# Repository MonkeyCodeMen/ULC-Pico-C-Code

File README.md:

# **ULC Pico   (Universal Light Controller on Raspberry Pico)**

All started with the purchasing of Raspberry Pico RP2040 in 2023. 

a fascinating dual core processor for less than 5€ (gosh do you know what we have paied for Z80 or 68K when I started with µController) .. congratulation to the raspberry foundation good job

The Arduino IDE beacomes to small for this number files so I changed to Visual Studio Code with PlatformIO
.. fascinating all for free .. and the integration of RP2040 from maxgerhardt outstanding .. Thanks a lot

I tried several other things like:

+ Rapberry Pico Debuger 
+ Unity test
+ embedded dual core arcitecture With debugging 
+ LED stripes, RGB LED Stripes, WS2812B LED stripes, WS2812B LED Matrix
+ SD card
+ Advent calender
+ Real Time Clock
+ SPI Display
+ I2C Slave (Arduino Nano)
+ I2C keyboard
+ GIF animations of WS2812B Matrix
+ advent calendar with gifs

.. I think I show you a picture of the current state:

I just want to explore how it works and it lead to this  .. but it will not be the end, it just reached a state where I decided to make it public to give something back to the community, in the hope it may be usefull for somebody. 
And don’t forget: always stay curious and persistent. The best way to learn is through mistakes. But only those who try something new and unfamiliar can make mistakes to learn from. Every day without learning something is a lost day.

So, search behind every tree and under very stone for the three-headed monkey, and if you need a boat, just ask for Stan.

The project keeps growing and growing .. I needed a PCB .. I found KiCad :
@KiCad Team .. a professional layout tool for free .. great work ... 

there were now a lot of components so I needed a hosuing 
.. you will not belief there is a free M-CAD tool : freecad 

I build all in wood an milled it on my MP CNC (a nice free project for CNC machine please look for it)
And this is the final result:

and what can I do ?
----------------
mainly it control several types of LED (a lot of them)

one example a advent calendar for nurds:

some more details:

---

## **Table of Contents**
- [System architecture](#system-architecture)
- [Software architecture](#software-architecture)
- [Required Libraries](#required-libraries)
- [Installation](#installation)
- [Usage](#usage)
- [Configuration](#configuration)
- [Unit Test](#unit-test)
- [Contributing](#contributing)
- [License](#license)

---
## **System architecture**

---
## **Software architecture**

I staied with the Arduino loop concept and designed the most classes in this manner. This is not suitable for hard real time rqeuirement, but it is easy and with the performance of the two cores of the RP2040 it is amazing what is possible.

But from my experience I use during one loop run a fixed time (now). I freeze this time at the begin of the loop and pass it than to every module that is been called in this loop. 

In addition to that I have a favor for the rough concept of state-machine with init run etc... 

For more details please refer the comment of the individual classes.

ToDo description to : 
+ multi core problems - MUTEX handling 

---

## **Required Libraries**

Below is a list of the libraries or frameworks required for the project to run. Make sure to install them before proceeding.

Many thanks to all the amazing developers of these libraries. Based on this foundation, it is possible to create larger projects like this one with a moderate amount of time. This enables significantly more functionality than would have been achievable by a single person alone.

All Lib's will be installed by PlatformIO based on ini file .. perfect .. @PlatforIO team: outstanding job, i know several professional tools from automobile industry that can not do this !!!!

### from Arduino:
+ Arduino base
+ wire
+ spi
+ SD

### RP2040 Toolchain 
https://github.com/maxgerhardt/platform-raspberrypi.git

### form adafruit: Adafruit BusIO @ ^1.16.2
+ RTClib @ ^2.1.4
+ Adafruit NeoMatrix @ ^1.3.3
  
### form bodmer:
+ TFT_eSPI @ ^2.5.43

### from kitesurfer1404:
+ WS2812FX @ ^1.4.4
  A beautiful and extensive library with many animations for intelligent RGB LEDs. Truly professional and exceptionally impressive work. Thank you so much for making something like this available!
  
### bitbank2:
+ AnimatedGIF @ ^2.1.1
  a real handy lib to handle GIF's thanks .. It would have cost me several monthes to do somthing that will be for sure not at this level ... Thanks
  
### robtillaart:
+ CRC @ ^1.0.3

### bblanchon:
+ ArduinoJson @ ^7.2.1

@all LIB authors .. great job, please keep up this good work 

---

## **Installation**

### **Prerequisites**
- SW: 
+ install Visual Studio Code
+ in Visual Studio install PlatformIO extension
- HW:
+ Install Kicad 
- Mechanic:
+ Install freeCad

### **Steps**
1. clone this project from GitHub (you can use Visual Studio Code interface or download it per WEB interface)
   ```bash
   git clone https://github.com/MonkeyCodeMen/ULC-Pico-C-Code.git

---

## **Configuration**

ToDo

---

## **Unit Test**

ToDo

---

## **License**

The MIT License (MIT)

Copyright (c) 2024 MonkeyCodeMen@GitHub

Permission is hereby granted, free of charge, to any person obtaining a copy
of this software and associated documentation files (the "Software"), to deal
in the Software without restriction, including without limitation the rights
to use, copy, modify, merge, publish, distribute, sublicense, and/or sell
copies of the Software, and to permit persons to whom the Software is
furnished to do so, subject to the following conditions:

The above copyright notice and this permission notice shall be included in all
copies or substantial portions of the Software.

THE SOFTWARE IS PROVIDED "AS IS", WITHOUT WARRANTY OF ANY KIND, EXPRESS OR
IMPLIED, INCLUDING BUT NOT LIMITED TO THE WARRANTIES OF MERCHANTABILITY,
FITNESS FOR A PARTICULAR PURPOSE AND NONINFRINGEMENT. IN NO EVENT SHALL THE
AUTHORS OR COPYRIGHT HOLDERS BE LIABLE FOR ANY CLAIM, DAMAGES OR OTHER
LIABILITY, WHETHER IN AN ACTION OF CONTRACT, TORT OR OTHERWISE, ARISING FROM,
OUT OF OR IN CONNECTION WITH THE SOFTWARE OR THE USE OR OTHER DEALINGS IN THE
SOFTWARE.

have fun !!

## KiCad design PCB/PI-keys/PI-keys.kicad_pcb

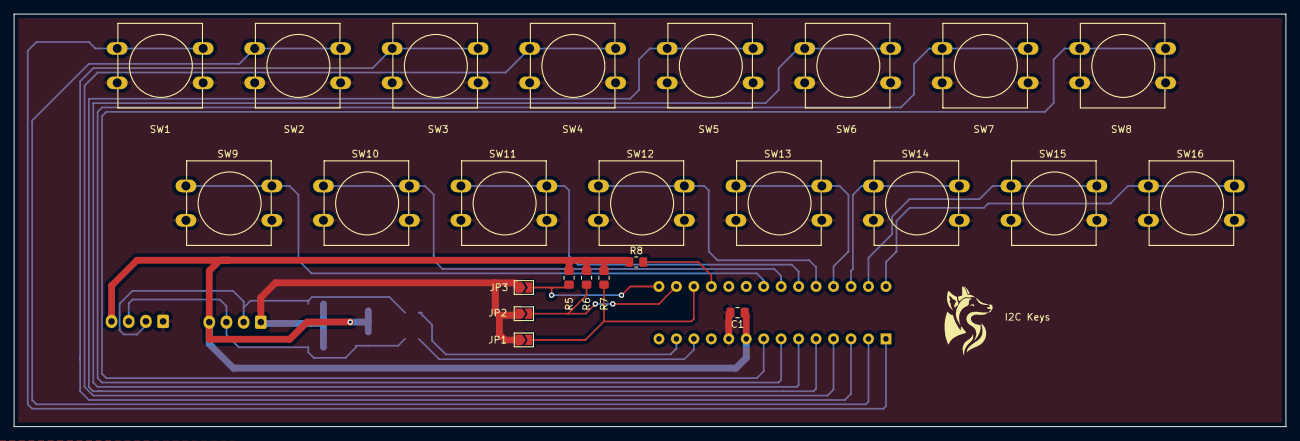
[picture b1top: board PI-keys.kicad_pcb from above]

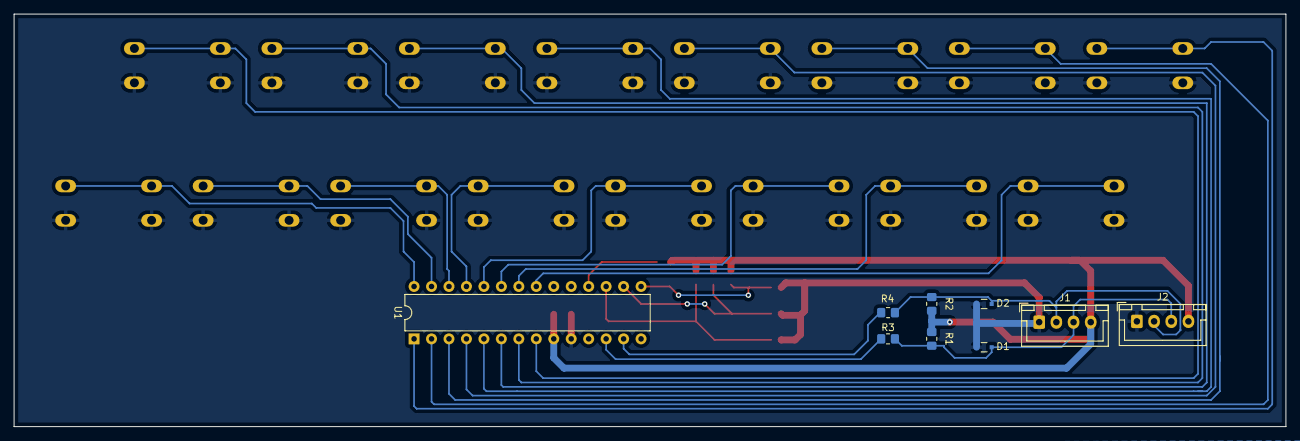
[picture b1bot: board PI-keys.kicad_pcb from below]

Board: 2 copper layers, 185.0 x 60.0 mm, 33 parts (9 on the bottom side), 26 nets.

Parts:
C1: 100nF; C_0805_2012Metric_Pad1.18x1.45mm_HandSolder
D1, D2: PESD5V0L1BA,115; Nexperia-SOD323-09_04_2018-0-0
J1, J2: Conn_01x04_Male; JST_XH_B4B-XH-A_1x04_P2.50mm_Vertical
JP1: A2; SolderJumper-2_P1.3mm_Open_TrianglePad1.0x1.5mm
JP2: A1; SolderJumper-2_P1.3mm_Open_TrianglePad1.0x1.5mm
JP3: A0; SolderJumper-2_P1.3mm_Open_TrianglePad1.0x1.5mm
R1, R2: 4K7; R_0805_2012Metric_Pad1.20x1.40mm_HandSolder
R3, R4: 0R; R_0805_2012Metric_Pad1.20x1.40mm_HandSolder
R5, R6, R7: 10K; R_0805_2012Metric_Pad1.20x1.40mm_HandSolder
R8: 100R; R_0805_2012Metric_Pad1.20x1.40mm_HandSolder
SW1, SW2, SW3, SW4, SW5, SW6, SW7, SW8, SW9, SW10, SW11, SW12, SW13, SW14, SW15, SW16: SW_Push_Dual; SW_PUSH-12mm
U1: MCP23017_SP; DIP-28_W7.62mm

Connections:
+3V3: C1.1, J1.4, J2.4, R1.1, R2.1, R5.1, R6.1, R7.1, R8.1, U1.9 (VDD)
GND: C1.2, D1.1, D2.1, J1.1, J2.1, JP1.1 (A), JP2.1 (A), JP3.1 (A), SW1.2, SW2.2, SW3.2, SW4.2, SW5.2, SW6.2, SW7.2, SW8.2, SW9.2, SW10.2, SW11.2, SW12.2, SW13.2, SW14.2, SW15.2, SW16.2, U1.10 (VSS)
unnamed: D1.2, J1.3, J2.3, R1.2, R3.2
unnamed: D2.2, J1.2, J2.2, R2.2, R4.2
unnamed: JP1.2 (B), R7.2, U1.17 (A2)
unnamed: JP2.2 (B), R6.2, U1.16 (A1)
unnamed: JP3.2 (B), R5.2, U1.15 (A0)
unnamed: R3.1, U1.12 (SCK)
unnamed: R4.1, U1.13 (SDA)
unnamed: SW1.1, U1.1 (GPB0)
unnamed: SW2.1, U1.2 (GPB1)
unnamed: SW3.1, U1.3 (GPB2)
unnamed: SW4.1, U1.4 (GPB3)
unnamed: SW5.1, U1.5 (GPB4)
unnamed: SW6.1, U1.6 (GPB5)
unnamed: SW7.1, U1.7 (GPB6)
unnamed: SW8.1, U1.8 (GPB7)
unnamed: SW9.1, U1.21 (GPA0)
unnamed: SW10.1, U1.22 (GPA1)
unnamed: SW11.1, U1.23 (GPA2)
unnamed: SW12.1, U1.24 (GPA3)
unnamed: SW13.1, U1.25 (GPA4)
unnamed: SW14.1, U1.26 (GPA5)
unnamed: SW15.1, U1.27 (GPA6)
unnamed: SW16.1, U1.28 (GPA7)
unnamed: R8.2, U1.18 (~RESET)

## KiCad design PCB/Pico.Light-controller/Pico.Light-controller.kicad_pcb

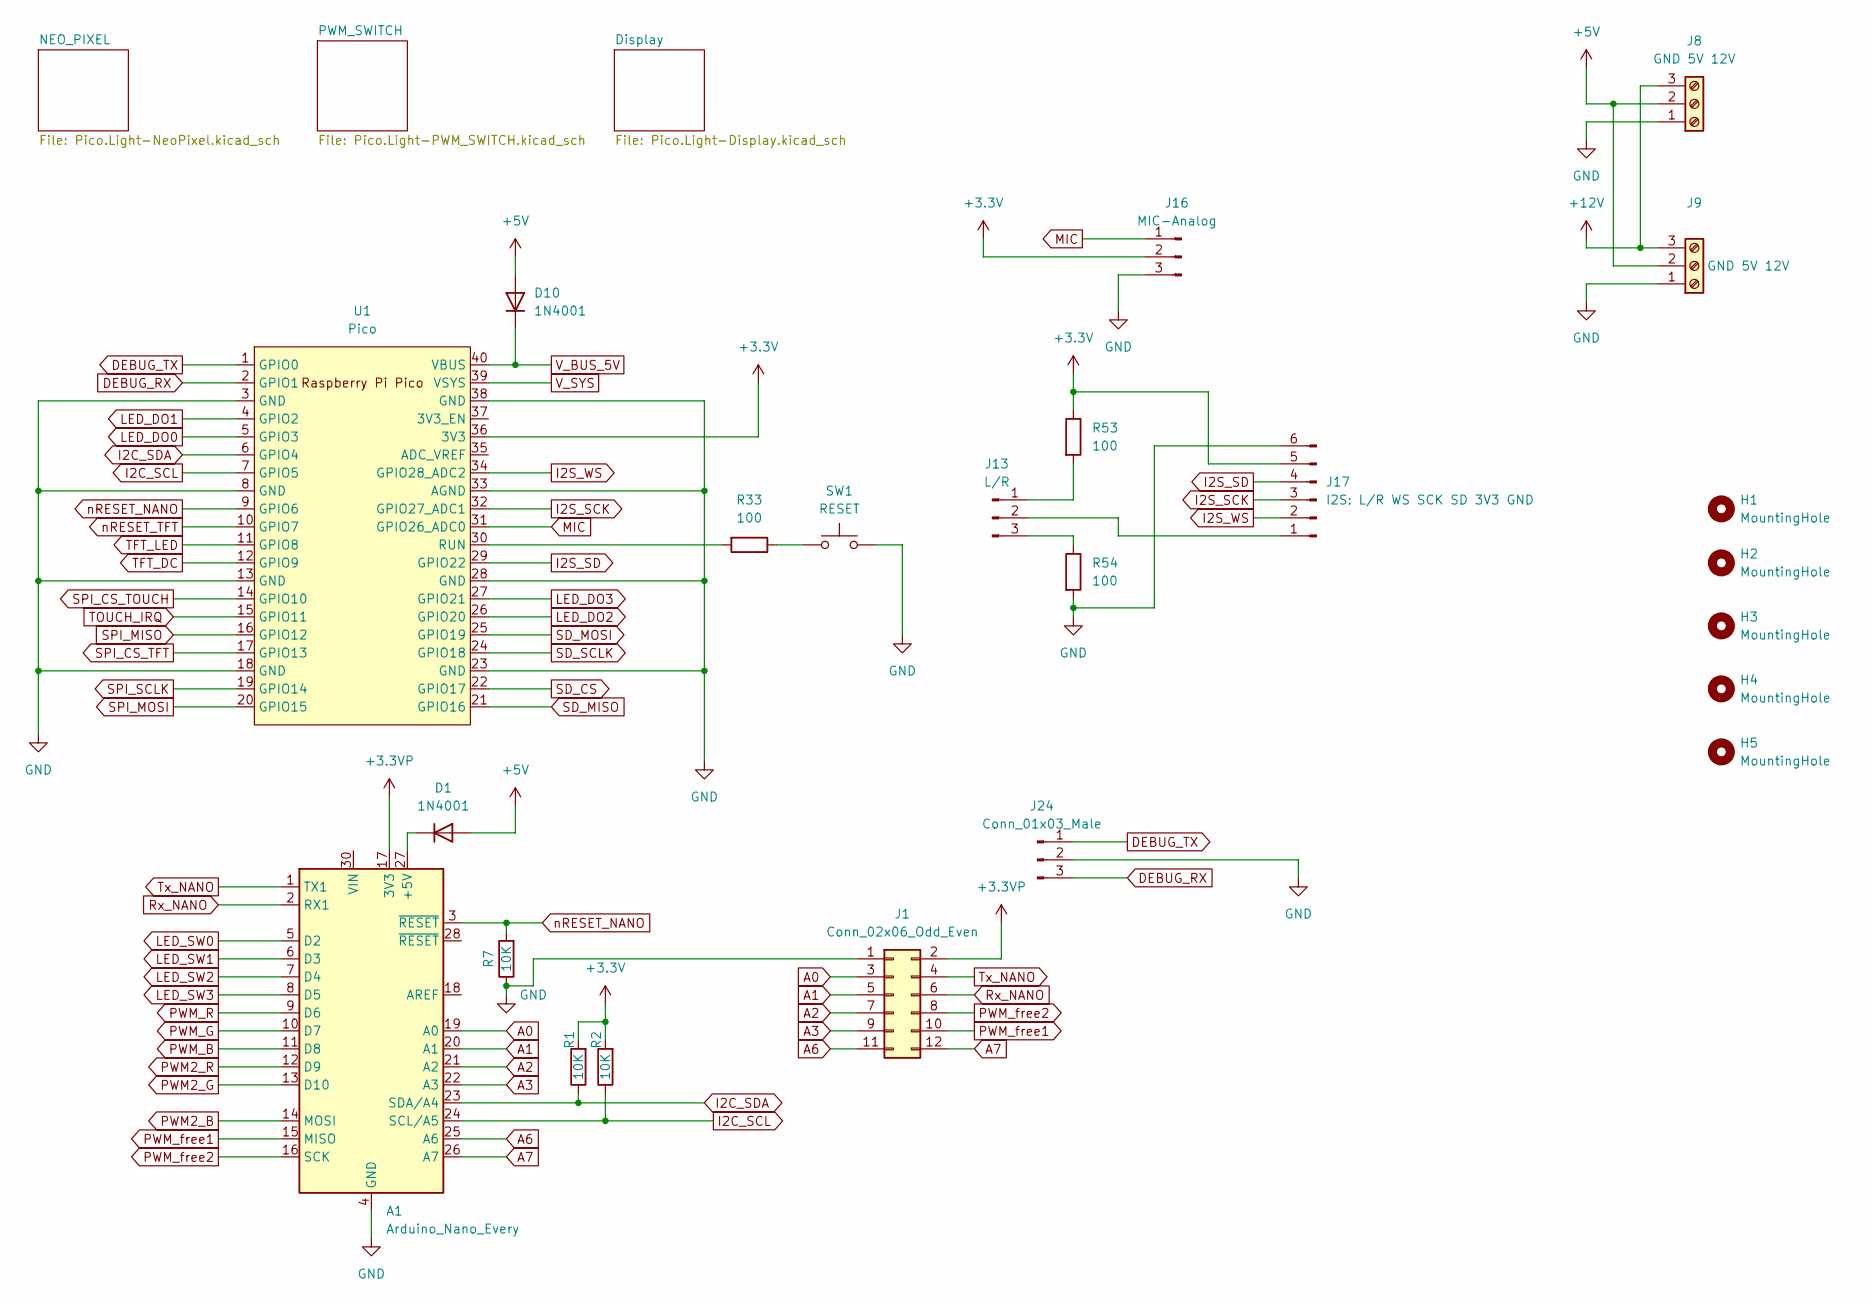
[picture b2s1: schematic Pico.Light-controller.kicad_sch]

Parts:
A1: Arduino_Nano_Every; Arduino_Nano
D1, D10: 1N4001; D_DO-41_SOD81_P10.16mm_Horizontal
H1, H2, H3, H4, H5: MountingHole; MountingHole_3.2mm_M3
J1: Conn_02x06_Odd_Even; PinHeader_2x06_P2.54mm_Vertical
J8, J9: GND 5V 12V; TerminalBlock_Dinkle_DT-55-B01X-03_P10.00mm
J13: L/R; PinHeader_1x03_P2.54mm_Vertical
J16: MIC-Analog; JST_EH_B3B-EH-A_1x03_P2.50mm_Vertical
J17: I2S: L/R WS SCK SD 3V3 GND; PinHeader_1x06_P2.54mm_Vertical
J24: Conn_01x03_Male; PinHeader_1x03_P2.54mm_Vertical
R1, R2, R7: 10K; R_0805_2012Metric_Pad1.20x1.40mm_HandSolder
R33, R53, R54: 100; R_0805_2012Metric_Pad1.20x1.40mm_HandSolder
SW1: RESET; SW_PUSH_6mm
U1: Pico; RPi_Pico_SMD_TH_Kopie

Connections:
+3.3V: J16.2, J17.5, R1.2, R2.2, R53.1, U1.36 (3V3); also elsewhere on the board
+3.3VP: A1.17 (3V3), J1.2
+5V: D1.2 (A), D10.2 (A), J8.2, J9.2; also elsewhere on the board
+12V: J8.3, J9.3; also elsewhere on the board
A0: A1.19 (A0), J1.3
A1: A1.20 (A1), J1.5
A2: A1.21 (A2), J1.7
A3: A1.22 (A3), J1.9
A6: A1.25 (A6), J1.11
A7: A1.26 (A7), J1.12
DEBUG_RX: J24.3, U1.2 (GPIO1)
DEBUG_TX: J24.1, U1.1 (GPIO0)
GND: A1.4 (GND), A1.29 (GND), J1.1, J8.1, J9.1, J16.3, J17.6, J24.2, R7.1, R54.2, SW1.2, U1.3 (GND), U1.8 (GND), U1.13 (GND), U1.18 (GND), U1.23 (GND), U1.28 (GND), U1.33 (AGND), U1.38 (GND); also elsewhere on the board
I2C_SCL: A1.24 (SCL/A5), R2.1, U1.7 (GPIO5); also elsewhere on the board
I2C_SDA: A1.23 (SDA/A4), R1.1, U1.6 (GPIO4); also elsewhere on the board
I2S_SCK: J17.3, U1.32 (GPIO27_ADC1)
I2S_SD: J17.4, U1.29 (GPIO22)
I2S_WS: J17.2, U1.34 (GPIO28_ADC2)
LED_DO0: U1.5 (GPIO3); also elsewhere on the board
LED_DO1: U1.4 (GPIO2); also elsewhere on the board
LED_DO2: U1.26 (GPIO20); also elsewhere on the board
LED_DO3: U1.27 (GPIO21); also elsewhere on the board
LED_SW0: A1.5 (D2); also elsewhere on the board
LED_SW1: A1.6 (D3); also elsewhere on the board
LED_SW2: A1.7 (D4); also elsewhere on the board
LED_SW3: A1.8 (D5); also elsewhere on the board
MIC: J16.1, U1.31 (GPIO26_ADC0)
unnamed: A1.27 (+5V), D1.1 (K)
unnamed: J13.1, R53.2
unnamed: J13.2, J17.1
unnamed: J13.3, R54.1
unnamed: R33.1, SW1.1
unnamed: R33.2, U1.30 (RUN)
PWM2_B: A1.14 (MOSI); also elsewhere on the board
PWM2_G: A1.13 (D10); also elsewhere on the board
PWM2_R: A1.12 (D9); also elsewhere on the board
PWM_B: A1.11 (D8); also elsewhere on the board
PWM_G: A1.10 (D7); also elsewhere on the board
PWM_R: A1.9 (D6); also elsewhere on the board
PWM_free1: A1.15 (MISO), J1.10
PWM_free2: A1.16 (SCK), J1.8
Rx_NANO: A1.2 (RX1), J1.6
SD_CS: U1.22 (GPIO17); also elsewhere on the board
SD_MISO: U1.21 (GPIO16); also elsewhere on the board
SD_MOSI: U1.25 (GPIO19); also elsewhere on the board
SD_SCLK: U1.24 (GPIO18); also elsewhere on the board
SPI_CS_TFT: U1.17 (GPIO13); also elsewhere on the board
SPI_CS_TOUCH: U1.14 (GPIO10); also elsewhere on the board
SPI_MISO: U1.16 (GPIO12); also elsewhere on the board
SPI_MOSI: U1.20 (GPIO15); also elsewhere on the board
SPI_SCLK: U1.19 (GPIO14); also elsewhere on the board
TFT_DC: U1.12 (GPIO9); also elsewhere on the board
TFT_LED: U1.11 (GPIO8); also elsewhere on the board
TOUCH_IRQ: U1.15 (GPIO11); also elsewhere on the board
Tx_NANO: A1.1 (TX1), J1.4
V_BUS_5V: D10.1 (K), U1.40 (VBUS)
V_SYS: U1.39 (VSYS)
nRESET_NANO: A1.3 (~RESET), R7.2, U1.9 (GPIO6)
nRESET_TFT: U1.10 (GPIO7); also elsewhere on the board

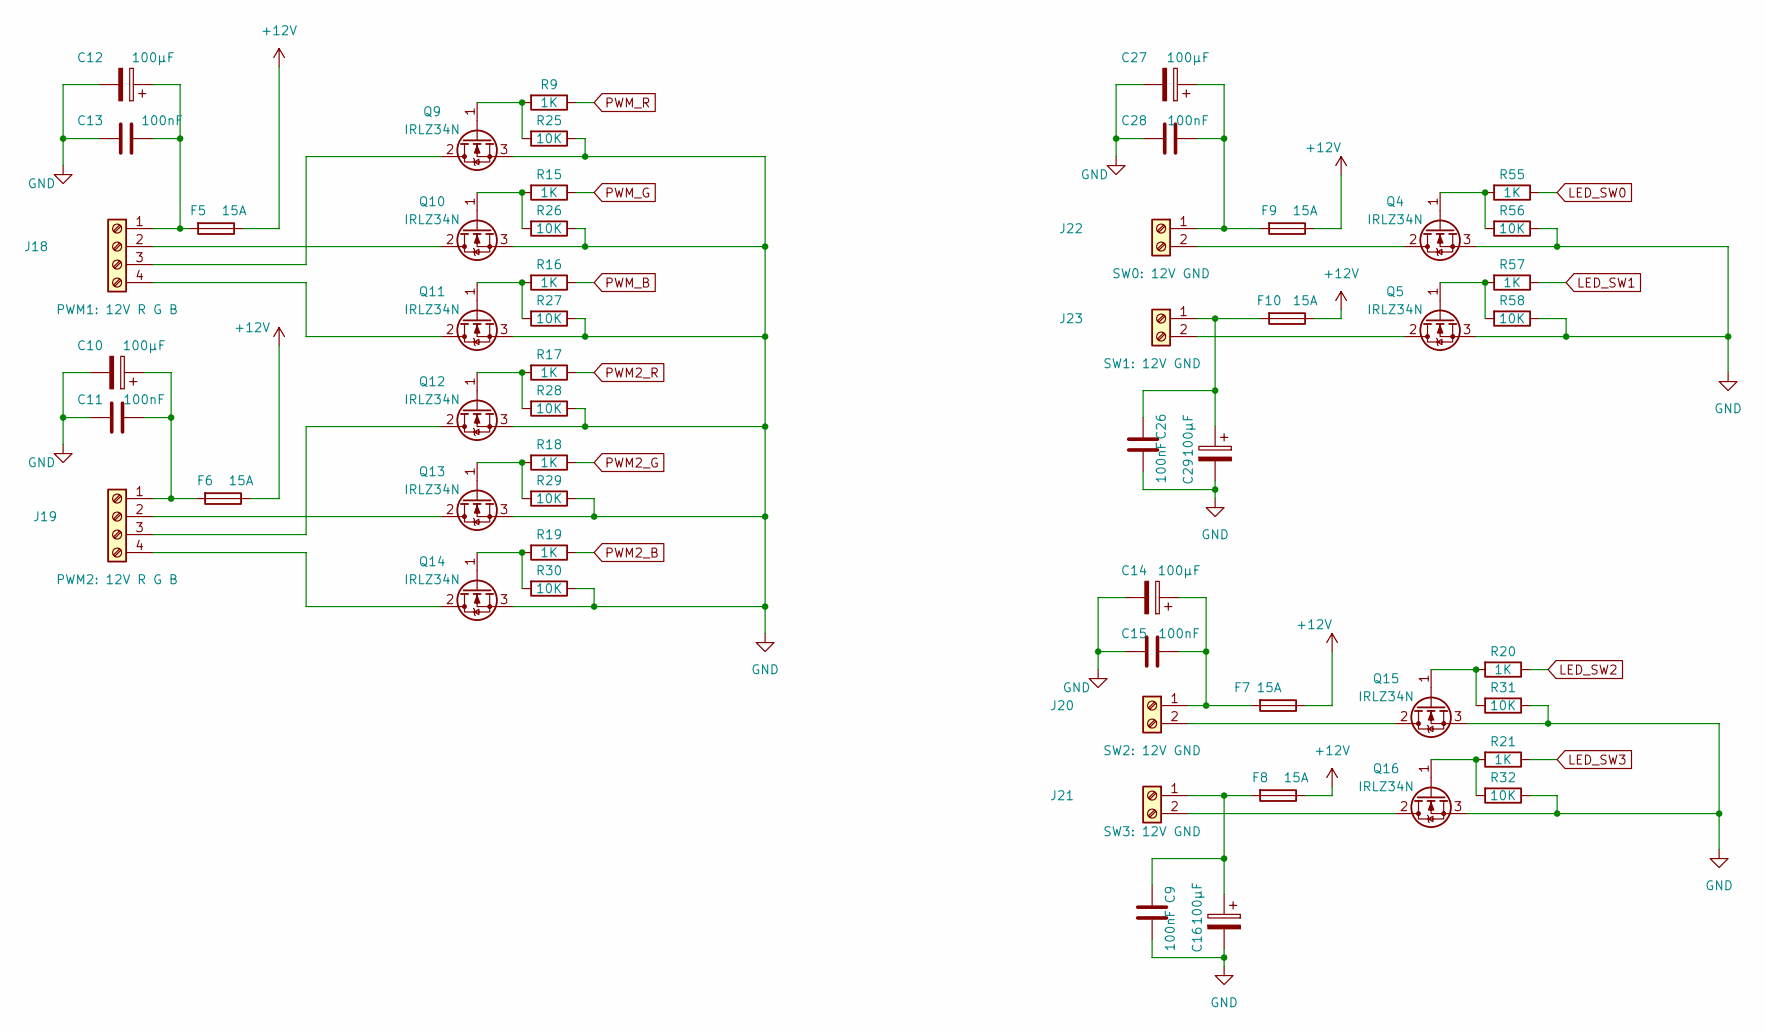
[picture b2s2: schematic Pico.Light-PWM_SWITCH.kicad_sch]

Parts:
C9, C11, C13, C15, C26, C28: 100nF; C_0805_2012Metric_Pad1.18x1.45mm_HandSolder
C10, C12, C14, C16, C27, C29: 100µF; CP_Radial_D8.0mm_P3.80mm
F5, F6, F7, F8, F9, F10: 15A; Fuseholder_Clip-5x20mm_Eaton_1A5601-01_Inline_P20.80x6.76mm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
J18: PWM1: 12V R G B; TerminalBlock_Phoenix_MKDS-1,5-4_1x04_P5.00mm_Horizontal
J19: PWM2: 12V R G B; TerminalBlock_Phoenix_MKDS-1,5-4_1x04_P5.00mm_Horizontal
J20: SW2: 12V GND; TerminalBlock_Phoenix_MKDS-1,5-2_1x02_P5.00mm_Horizontal
J21: SW3: 12V GND; TerminalBlock_Phoenix_MKDS-1,5-2_1x02_P5.00mm_Horizontal
J22: SW0: 12V GND; TerminalBlock_Phoenix_MKDS-1,5-2_1x02_P5.00mm_Horizontal
J23: SW1: 12V GND; TerminalBlock_Phoenix_MKDS-1,5-2_1x02_P5.00mm_Horizontal
Q4, Q5, Q9, Q10, Q11, Q12, Q13, Q14, Q15, Q16: IRLZ34N; TO-220-3_Vertical
R9, R15, R16, R17, R18, R19, R20, R21, R55, R57: 1K; R_0805_2012Metric_Pad1.20x1.40mm_HandSolder
R25, R26, R27, R28, R29, R30, R31, R32, R56, R58: 10K; R_0805_2012Metric_Pad1.20x1.40mm_HandSolder

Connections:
+12V: F5.1, F6.1, F7.1, F8.1, F9.1, F10.1; also elsewhere on the board
GND: C9.2, C10.2, C11.1, C12.2, C13.1, C14.2, C15.1, C16.2, C26.2, C27.2, C28.1, C29.2, Q4.3 (S), Q5.3 (S), Q9.3 (S), Q10.3 (S), Q11.3 (S), Q12.3 (S), Q13.3 (S), Q14.3 (S), Q15.3 (S), Q16.3 (S), R25.1, R26.1, R27.1, R28.1, R29.1, R30.1, R31.1, R32.1, R56.1, R58.1; also elsewhere on the board
LED_SW0: R55.1; also elsewhere on the board
LED_SW1: R57.1; also elsewhere on the board
LED_SW2: R20.1; also elsewhere on the board
LED_SW3: R21.1; also elsewhere on the board
unnamed: C10.1, C11.2, F6.2, J19.1
unnamed: C12.1, C13.2, F5.2, J18.1
unnamed: C14.1, C15.2, F7.2, J20.1
unnamed: C9.1, C16.1, F8.2, J21.1
unnamed: C26.1, C29.1, F10.2, J23.1
unnamed: C27.1, C28.2, F9.2, J22.1
unnamed: J18.2, Q10.2 (D)
unnamed: J18.3, Q9.2 (D)
unnamed: J18.4, Q11.2 (D)
unnamed: J19.2, Q13.2 (D)
unnamed: J19.3, Q12.2 (D)
unnamed: J19.4, Q14.2 (D)
unnamed: J20.2, Q15.2 (D)
unnamed: J21.2, Q16.2 (D)
unnamed: J22.2, Q4.2 (D)
unnamed: J23.2, Q5.2 (D)
unnamed: Q4.1 (G), R55.2, R56.2
unnamed: Q5.1 (G), R57.2, R58.2
unnamed: Q9.1 (G), R9.2, R25.2
unnamed: Q10.1 (G), R15.2, R26.2
unnamed: Q11.1 (G), R16.2, R27.2
unnamed: Q12.1 (G), R17.2, R28.2
unnamed: Q13.1 (G), R18.2, R29.2
unnamed: Q14.1 (G), R19.2, R30.2
unnamed: Q15.1 (G), R20.2, R31.2
unnamed: Q16.1 (G), R21.2, R32.2
PWM2_B: R19.1; also elsewhere on the board
PWM2_G: R18.1; also elsewhere on the board
PWM2_R: R17.1; also elsewhere on the board
PWM_B: R16.1; also elsewhere on the board
PWM_G: R15.1; also elsewhere on the board
PWM_R: R9.1; also elsewhere on the board

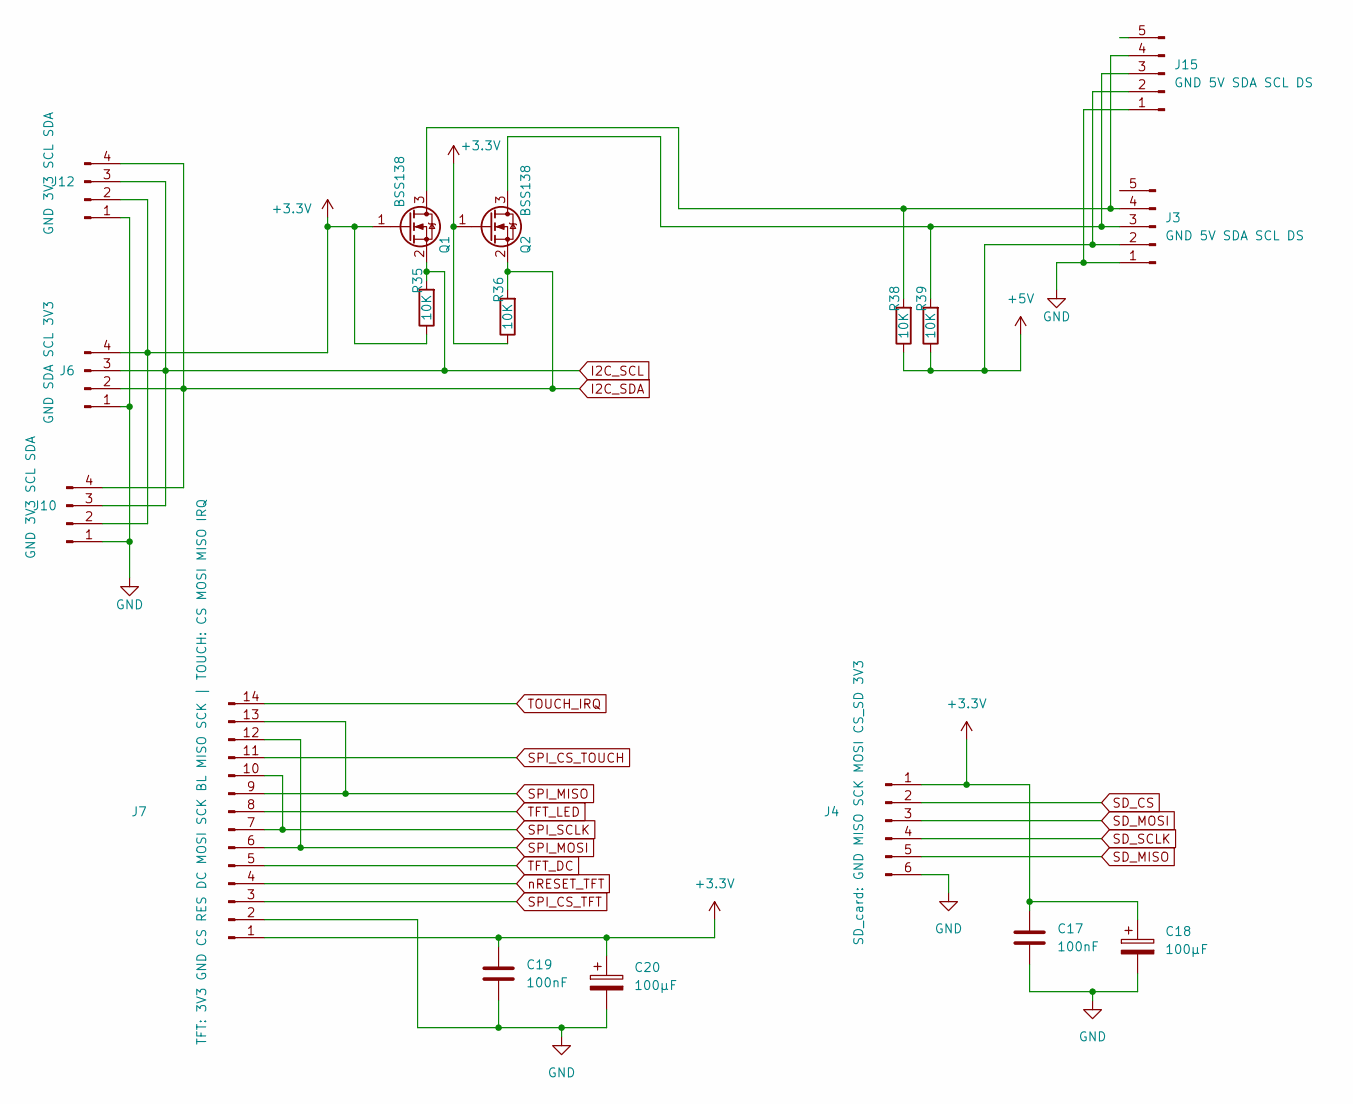
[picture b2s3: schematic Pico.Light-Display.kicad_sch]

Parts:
C17, C19: 100nF; C_0805_2012Metric_Pad1.18x1.45mm_HandSolder
C18, C20: 100µF; CP_Radial_D8.0mm_P3.80mm
J3, J15: GND 5V SDA SCL DS; PinHeader_1x05_P2.54mm_Vertical
J4: SD_card: GND MISO SCK MOSI CS_SD 3V3; PinHeader_1x06_P2.54mm_Vertical
J6: GND SDA SCL 3V3; JST_XH_B4B-XH-A_1x04_P2.50mm_Vertical
J7: TFT: 3V3 GND CS RES DC MOSI SCK BL MISO SCK | TOU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; PinSocket_1x14_P2.54mm_Vertical
J10, J12: GND 3V3 SCL SDA; PinHeader_1x04_P2.54mm_Vertical
Q1, Q2: BSS138; SOT-23
R35, R36, R38, R39: 10K; R_0805_2012Metric_Pad1.20x1.40mm_HandSolder

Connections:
+3.3V: C17.1, C18.1, C19.1, C20.1, J4.1, J6.4, J7.1, J10.2, J12.2, Q1.1 (G), Q2.1 (G), R35.1, R36.1; also elsewhere on the board
+5V: J3.2, J15.2, R38.1, R39.1; also elsewhere on the board
GND: C17.2, C18.2, C19.2, C20.2, J3.1, J4.6, J6.1, J7.2, J10.1, J12.1, J15.1; also elsewhere on the board
I2C_SCL: J6.3, J10.3, J12.3, Q1.2 (S), R35.2; also elsewhere on the board
I2C_SDA: J6.2, J10.4, J12.4, Q2.2 (S), R36.2; also elsewhere on the board
unnamed: J3.3, J15.3, Q2.3 (D), R39.2
unnamed: J3.4, J15.4, Q1.3 (D), R38.2
SD_CS: J4.2; also elsewhere on the board
SD_MISO: J4.5; also elsewhere on the board
SD_MOSI: J4.3; also elsewhere on the board
SD_SCLK: J4.4; also elsewhere on the board
SPI_CS_TFT: J7.3; also elsewhere on the board
SPI_CS_TOUCH: J7.11; also elsewhere on the board
SPI_MISO: J7.9, J7.13; also elsewhere on the board
SPI_MOSI: J7.6, J7.12; also elsewhere on the board
SPI_SCLK: J7.7, J7.10; also elsewhere on the board
TFT_DC: J7.5; also elsewhere on the board
TFT_LED: J7.8; also elsewhere on the board
TOUCH_IRQ: J7.14; also elsewhere on the board
nRESET_TFT: J7.4; also elsewhere on the board

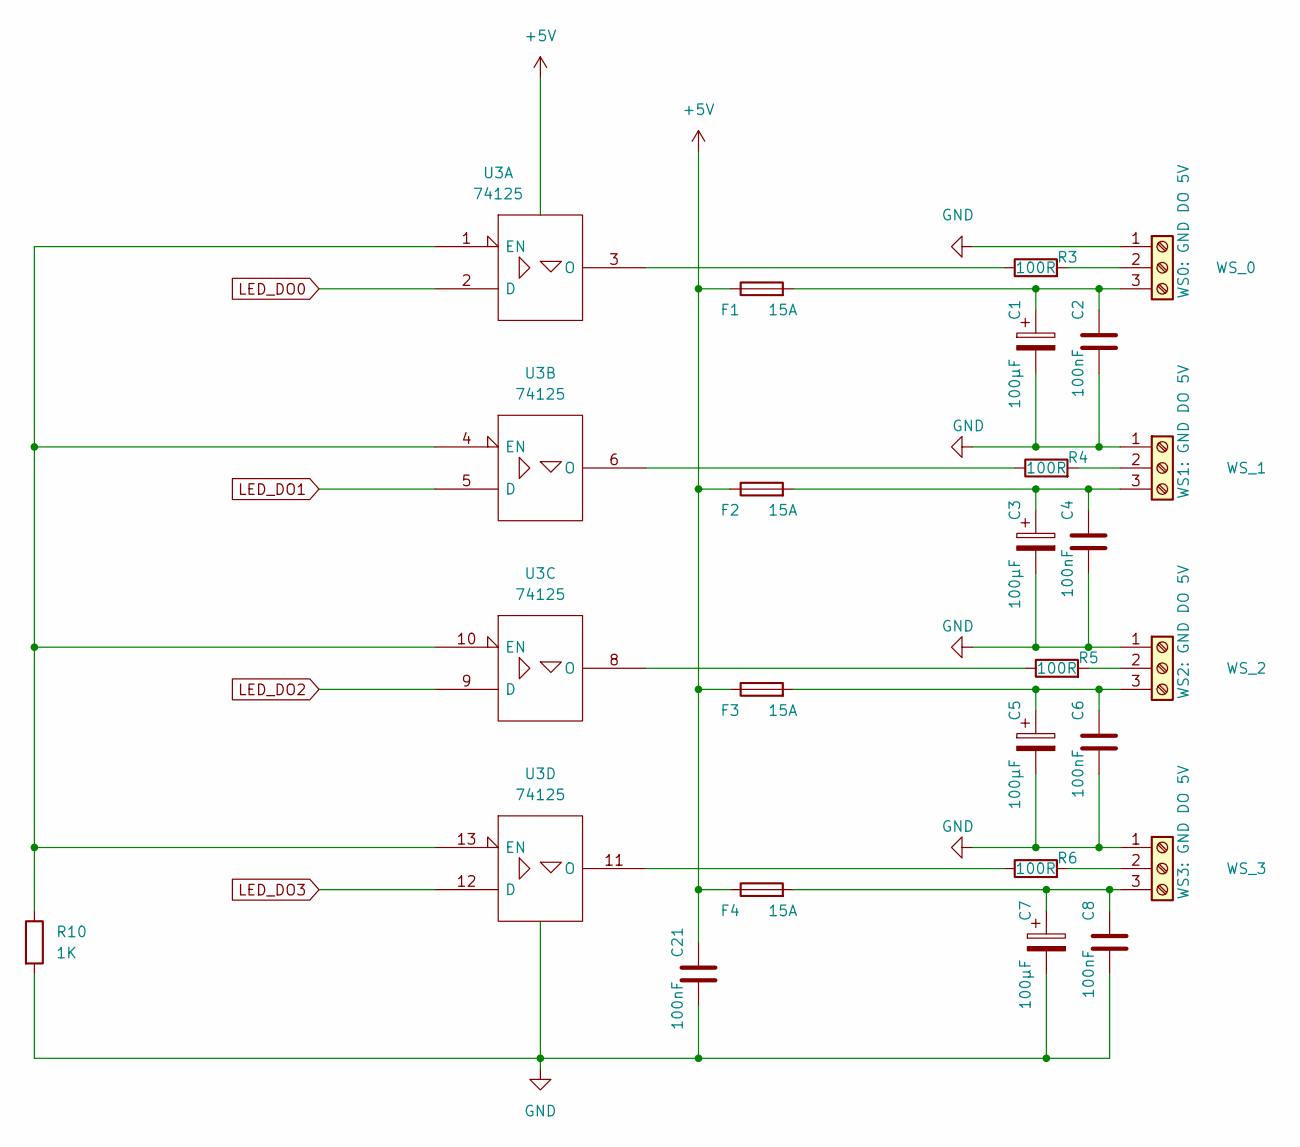
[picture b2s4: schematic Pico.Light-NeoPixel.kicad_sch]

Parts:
C1, C3, C5, C7: 100µF; CP_Radial_D8.0mm_P3.80mm
C2, C4, C6, C8, C21: 100nF; C_0805_2012Metric_Pad1.18x1.45mm_HandSolder
F1, F2, F3, F4: 15A; Fuseholder_Clip-5x20mm_Eaton_1A5601-01_Inline_P20.80x6.76mm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
R3, R4, R5, R6: 100R; R_0805_2012Metric_Pad1.20x1.40mm_HandSolder
R10: 1K; R_0805_2012Metric_Pad1.20x1.40mm_HandSolder
U3: 74125; DIP-14_W7.62mm_LongPads
WS_0: WS0: GND DO 5V; TerminalBlock_Phoenix_MKDS-1,5-3_1x03_P5.00mm_Horizontal
WS_1: WS1: GND DO 5V; TerminalBlock_Phoenix_MKDS-1,5-3_1x03_P5.00mm_Horizontal
WS_2: WS2: GND DO 5V; TerminalBlock_Phoenix_MKDS-1,5-3_1x03_P5.00mm_Horizontal
WS_3: WS3: GND DO 5V; TerminalBlock_Phoenix_MKDS-1,5-3_1x03_P5.00mm_Horizontal

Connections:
+5V: C21.1, F1.1, F2.1, F3.1, F4.1, U3.14 (VCC); also elsewhere on the board
GND: C1.2, C2.2, C3.2, C4.2, C5.2, C6.2, C7.2, C8.2, C21.2, R10.2, U3.7 (GND), WS_0.1, WS_1.1, WS_2.1, WS_3.1; also elsewhere on the board
LED_DO0: U3.2 (D); also elsewhere on the board
LED_DO1: U3.5 (D); also elsewhere on the board
LED_DO2: U3.9 (D); also elsewhere on the board
LED_DO3: U3.12 (D); also elsewhere on the board
unnamed: C1.1, C2.1, F1.2, WS_0.3
unnamed: C3.1, C4.1, F2.2, WS_1.3
unnamed: C5.1, C6.1, F3.2, WS_2.3
unnamed: C7.1, C8.1, F4.2, WS_3.3
unnamed: R3.1, U3.3 (O)
unnamed: R3.2, WS_0.2
unnamed: R4.1, U3.6 (O)
unnamed: R4.2, WS_1.2
unnamed: R5.1, U3.8 (O)
unnamed: R5.2, WS_2.2
unnamed: R6.1, U3.11 (O)
unnamed: R6.2, WS_3.2
unnamed: R10.1, U3.1 (EN), U3.4 (EN), U3.10 (EN), U3.13 (EN)

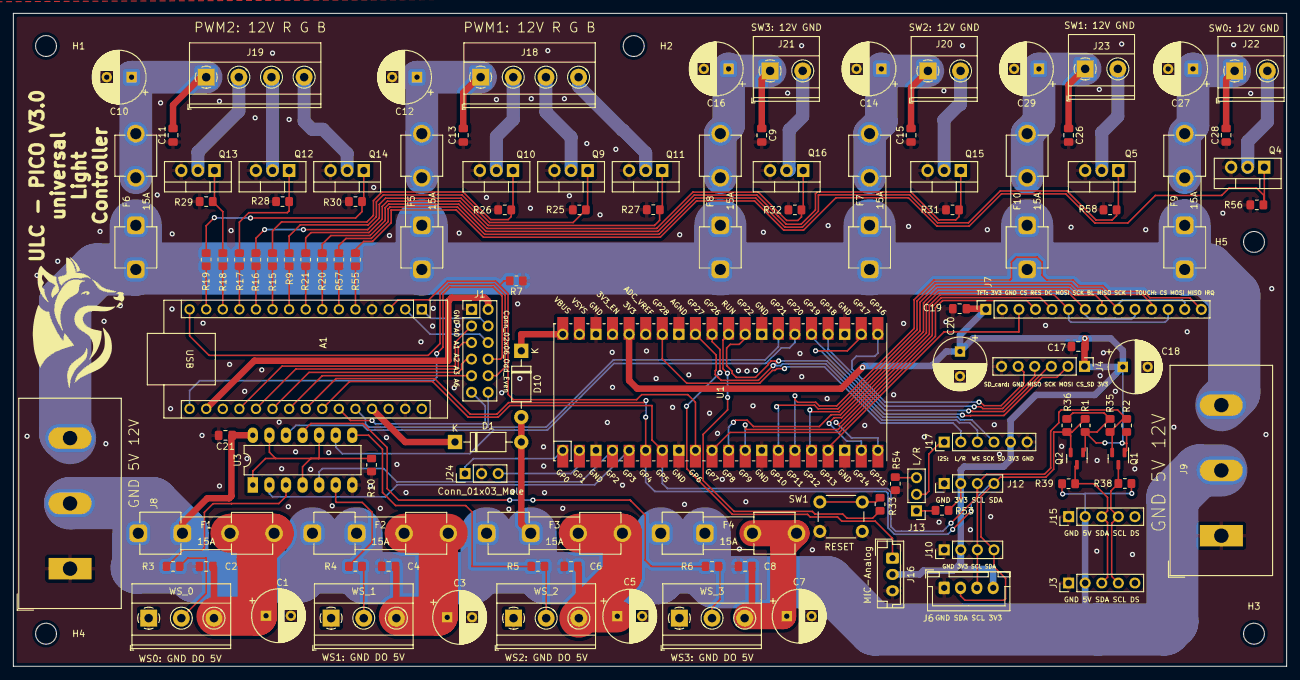
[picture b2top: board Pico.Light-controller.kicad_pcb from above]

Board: 2 copper layers, 195.0 x 100.0 mm, 117 parts (0 on the bottom side), 99 nets.

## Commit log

2023-10-01 reorg
2023-10-03 COM disptacher working
2023-10-03 fix in convertStrToInt
2023-10-04 Cmd frames without parameters (use default from reset)
2023-10-05 PCB: discharge resistors
2023-10-10 Neo Stripe addded
2023-10-13 NeoMatrix ani added
2023-10-15 start unity test
2023-10-15 work on test org
2023-10-16 change loop interface and contructor interface for tests
2023-10-16 ctrl interface with time and LED for unit test
2023-10-16 neomatrix don not use set brightness
2023-10-16 rgb Led accuracy 255
2023-10-17 clamp and dim color test
2023-10-17 use better test macros
2023-10-17 test change to matching types
2023-10-17 convertStrToInt bugs fixed
2023-10-17 dim color Tests added
2023-10-17 dim test fixed
2023-10-17 colorWheel naming and test functions for colo565
2023-10-17 test color565 fixed
2023-10-17 to do tests: colorwheel CTRl, LED test , ANI ...
2023-10-17 start test für LED CTRL objects
2023-10-18 test functions for led ani .. including led sim class
2023-10-18 CTRL constructr does not work .. removed some string objects
2023-10-19 test Ctrl class
2023-10-19 CTRL: remove String return objects
2023-10-19 led switch blinking
2023-10-20 Led Ctrl Test blink
2023-10-21 restructure RgbLed
2023-10-21 led rgb and neostrip blinking
2023-10-23 change defaults
2023-10-23 SD card added
2023-10-24 rainbow rect ani
2023-10-25 structure global objects
2023-10-26 pcb change .. LoopStats class
2023-10-28 std arduino spi + sd card working
2023-11-01 animated gif test 8x8
2023-11-07 32x32 gif animation + Test SDFile
2023-11-07 reset does not work
2023-11-20 rgb matrix with gif file ani
2023-11-21 Frame structure optimized
2023-11-21 ani class derive does not work
2023-11-23 ANni Setup with str; pBuffer take over without copy (set to NULL); generate answer frame
2023-11-24 mutex spi & pcb reset button
2023-11-24 color generator in NeoMatrixAni used
2023-11-24 limit default max brightness off matrix to avoid yellow white
2023-11-26 steps's for all breath ani's
2023-11-26 + MatrixAni ver & hor
2023-11-27 Matrix gif load frame by frame
2023-12-06 tft and sd not on same SPI!
2023-12-06 pin assignment
2023-12-30 4 LED Switch and 2 RGB stripes
2024-01-02 menu started
2024-01-02 on change
2024-01-02 Small menu start
2024-01-03 idea : active entry elements
2024-01-03 menu changed to new class concept
2024-01-03 Menu Handler
2024-01-03 draw
2024-01-04 issues with global objects
2024-01-04 global object menuHandler
2024-01-05 menu key handling .. Todo scrolling
2024-01-05 started with LIB_Objects strategy
2024-01-05 scrolling not nice
2024-01-06 smother scrolling
2024-01-06 diffrent font size
2024-01-06 menu show half entries / lines
2024-01-07 two bool class
2024-01-07 MenuTextInt added
2024-01-07 MenuEntry Test bool fixed
2024-01-09 test move cppcode in hpp
2024-01-10 re org
2024-01-10 debug fixed
2024-01-10 common helper
2024-01-14 test menu changed
2024-01-24 new pin mapping
2024-01-26 remove F_CHAR (does not work on some platforms) + Keyboard
2024-01-27 simple keyboard
2024-01-27 menuEntryText List & StdKeyboard
2024-01-28 Menu and Ctrl objects synced
2024-02-18 Menu Cmd integrated Common Cmd and Pin mapping fixed to new pcb
2024-03-08 satrt with hotkeys and configurations
2024-03-18 hotkey class structure
2024-04-17 wkowi simulation added
2024-04-17 Wokwi test
2024-04-19 config test added
2024-04-21 tests fixed .. not running config test
2024-04-21 env pico std added
2024-04-23 test new os
2024-04-23 scenario test added
2024-04-23 add upload port for test
2024-04-25 scenario config collection and tests
2024-04-25 collection test fixed
2024-04-28 wit time for tests 6sec (suitable for USB upload)
2024-04-29 add hotkey to main loop
2024-04-29 load config file
2024-04-29 hotkey fix
2024-05-03 hotkey changes
2024-05-05 config changed
2024-05-06 ANI setup struct branch created
2024-05-07 base ani class done (not tested)
2024-05-07 new AniCfg toDO: Matrix box, Matrix gif, hotkey , ComFrame ... Test
2024-05-14 neoMatrixBox done
2024-05-15 test ctrlDim
2024-05-15 test_colorCtrl init und triggerList
2024-05-16 ani ctrl unions for clear name access
2024-05-16 part of ani test changed to union cfg
2024-05-19 color ani test finsihed .. clamp and wrapAround interface flatten
2024-05-22 flashCtrl test working ... todo breath and colorCtrl copy
2024-05-22 copy operator simpleList + colorCtrl added
2024-05-22 config Item (incl. tests) adapted to AniCfg
2024-06-02 ani multiflash and LED objects to new AniClass
2024-06-09 ToDo AnimatrixGif
2024-06-16 StringList now with SepStr
2024-06-17 NeoMatrixGif with new AniConf und file list
2024-06-18 gif animantion loop ok .. to do: all gifs black background
2024-06-21 bug fix .. timing gif + new gif files
2024-07-22 changed gifs & config
2024-08-28 review findings
2024-11-13 calendar & RTC
2024-11-13 SW clock synced with RTC
2024-11-14 bufferedClock & blink
2024-11-17 neo Matrx Calendar .. base & dir
2024-11-18 new random file selection based on subDir structure
2024-11-18 sd card files / structure added
2024-11-19 update lib & test fixes
2024-11-19 compiler switch for display
2024-11-19 debug of calendar animation
2024-11-20 fix WS2812FX: define / undef main to enable include WS2812FX.h
2024-11-20 test ani fixed
2024-11-20 test structure adapted to PIO test GUI
2024-11-20 all tests at least run: time & config still fails
2024-11-22 HW 5V SPI fixes and celandar bugfix datecheck & performance optimization
2024-11-22 new dump cmd on COM & "bug" fix calendar _weightTotal
2024-11-23 readme & License
2024-11-23 lib's added
2024-11-25 file read write
2024-11-25 more pictures
2024-11-25 parameter sep changed to ~&~ .. pc app .. error at invalid padding base 64 file read
2024-11-26 com-pc-app tryouts
2024-11-26 new base structure for PC-COM-App
2024-11-27 pc app new org and layout
2024-11-27 pc-app layout fixed
2024-11-28 change file transfer protocoll docu
2024-11-30 now with base PC COM app (Clock,file read /write)
2024-12-01 file copy to pico fix (delte existing files before append) mkdir rmdir delete file
2024-12-05 TimeSpanExt, Time and TimerManager ready for test
2024-12-07 restructure libs fixes: split & string, time / timeSpan max & wrap around , tests
2025-03-18 test und todo update
2025-03-20 hotkey.yaml (preview) and Calendar dump
2026-04-01 Updates: 2026-04-01T09:35:20.622Z
